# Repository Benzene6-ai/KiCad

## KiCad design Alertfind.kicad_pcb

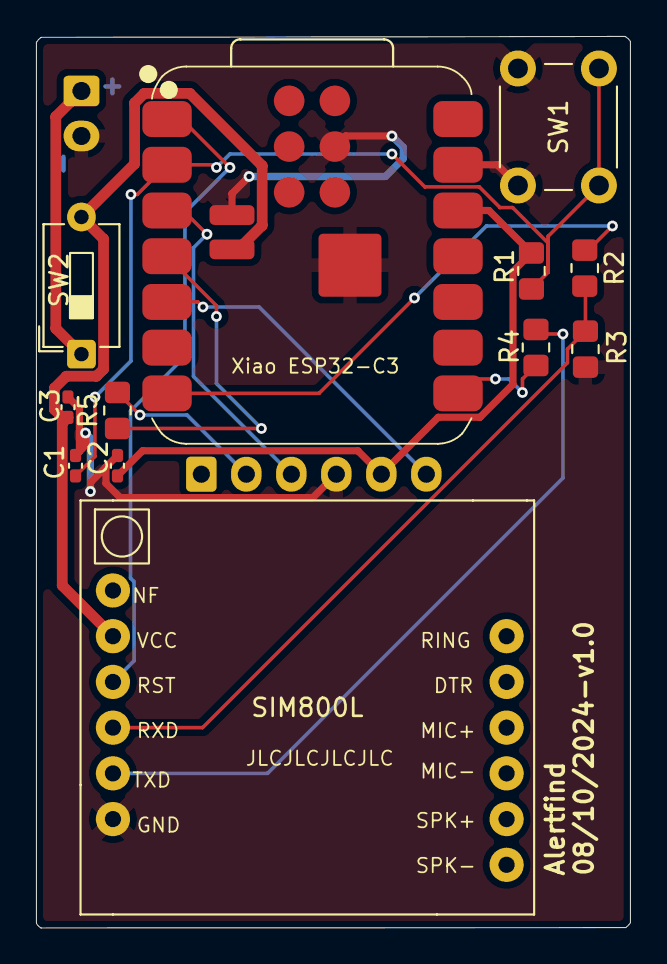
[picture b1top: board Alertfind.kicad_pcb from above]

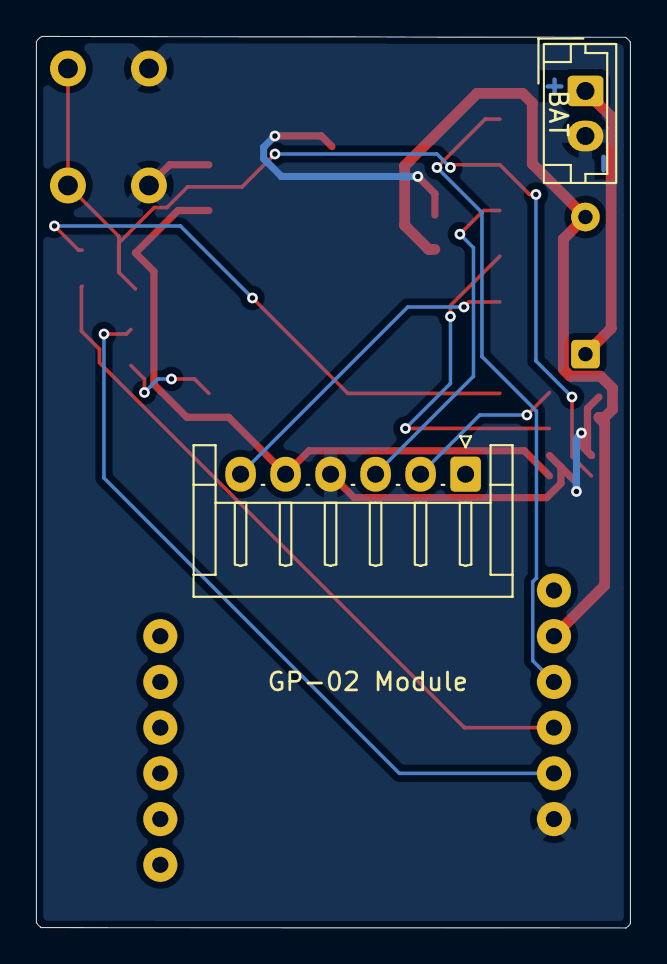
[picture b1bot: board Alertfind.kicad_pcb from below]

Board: 2 copper layers, 33.0 x 49.5 mm, 14 parts (2 on the bottom side), 14 nets.

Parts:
BAT: Conn_01x02_Socket; JST_EH_B2B-EH-A_1x02_P2.50mm_Vertical
C1, C2: 100nF; C_0402_1005Metric_Pad0.74x0.62mm_HandSolder
C3: 1000uF; C_0402_1005Metric_Pad0.74x0.62mm_HandSolder
GP-02 Module: GP-02 module; JST_EH_S6B-EH_1x06_P2.50mm_Horizontal
R1: 10k; R_0805_2012Metric_Pad1.20x1.40mm_HandSolder
R2, R4: 1k; R_0805_2012Metric_Pad1.20x1.40mm_HandSolder
R3: 2k; R_0805_2012Metric_Pad1.20x1.40mm_HandSolder
R5: 100; R_0805_2012Metric_Pad1.20x1.40mm_HandSolder
SIM800L: SIM800L-CORE
SW1: SW_Push; SW_PUSH_6mm
SW2: SW_SPST; SW_DIP_SPSTx01_Slide_6.7x4.1mm_W7.62mm_P2.54mm_LowProfile
Xiao ESP32-C3: XIAO-ESP32-C3-SMD

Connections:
+3.3V: C2.1, GP-02 Module.5, R1.1, Xiao ESP32-C3.12 (3V3_OUT)
+BATT: C3.1, SIM800L.2 (VCC), SW2.2 (B), Xiao ESP32-C3.21 (VBAT)
GND: BAT.2, C1.2, C2.2, C3.2, GP-02 Module.4, R3.2, SIM800L.6 (GND), SW1.1, Xiao ESP32-C3.13 (GND), Xiao ESP32-C3.18 (GND), Xiao ESP32-C3.22 (GND), Xiao ESP32-C3.23 (PAD)
unnamed: GP-02 Module.2, R5.2
unnamed: GP-02 Module.3, Xiao ESP32-C3.3 (D2)
unnamed: GP-02 Module.6, Xiao ESP32-C3.5 (D4)
unnamed: BAT.1, SW2.1 (A)
unnamed: SIM800L.3 (RST), Xiao ESP32-C3.1 (D0)
unnamed: C1.1, R1.2, SW1.2, Xiao ESP32-C3.2 (D1)
unnamed: R5.1, Xiao ESP32-C3.4 (D3)
unnamed: R2.1, Xiao ESP32-C3.7 (D6)
unnamed: R4.1, Xiao ESP32-C3.8 (D7)
unnamed: R2.2, R3.1, SIM800L.4 (RXD)
unnamed: R4.2, SIM800L.5 (TXD)

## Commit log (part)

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2026-04-16 Add files via upload
    First commit - Erste vesuch
